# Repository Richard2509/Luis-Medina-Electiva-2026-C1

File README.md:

# Luis-Medina-Electiva-2026-C1
##  Tarea – Resumen de MBSE

En este repositorio se encuentra el resumen correspondiente a la asignatura **Electiva 2026 C1**, sobre el tema **Model-Based Systems Engineering (MBSE)** y tambien se encuentra el link de un video que tambien forma parte de la tarea.

 **Archivo adjunto:**
[Resumen de MBSE.zip](https://github.com/user-attachments/files/24985662/Resumen.de.MBSE.zip)

**Link del Video**
https://youtu.be/C6BTCFWo2lI?si=XBMWATvWH2EMt3oG

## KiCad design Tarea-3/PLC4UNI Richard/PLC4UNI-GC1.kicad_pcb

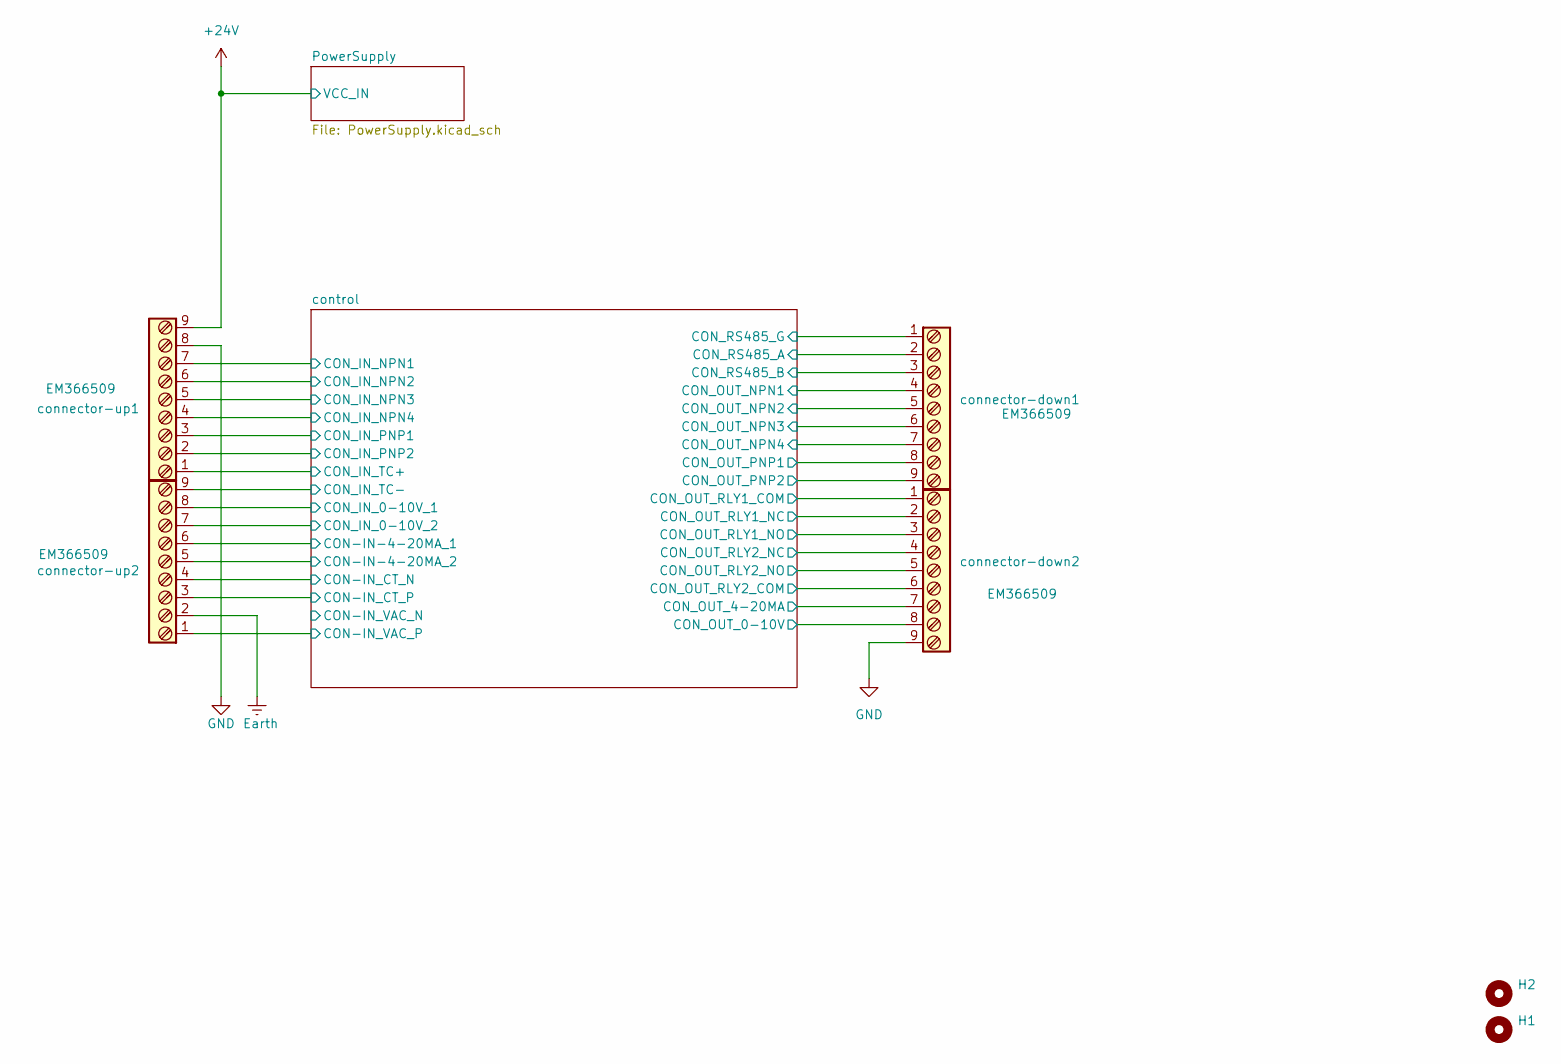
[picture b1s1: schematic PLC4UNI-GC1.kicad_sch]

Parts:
H1, H2: MountingHole; MountingHole_3.2mm_M3
connector-down1, connector-down2: Screw_Terminal_9_P5.00mm; TerminalBlock_Phoenix_PT-1,5-9-5.0-H_1x09_P5.00mm_Horizontal; Part number EM366509
connector-up1, connector-up2: Screw_Terminal_9_P5.00mm; TerminalBlock_Phoenix_PT-1,5-9-5.0-H_1x09_P5.00mm_Horizontal; Part number EM366509

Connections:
+24V: connector-up1.9; also elsewhere on the board
/control/CON-IN-4-20MA_1: connector-up2.6; also elsewhere on the board
/control/CON-IN-4-20MA_2: connector-up2.5; also elsewhere on the board
/control/CON-IN_CT_N: connector-up2.4; also elsewhere on the board
/control/CON-IN_CT_P: connector-up2.3; also elsewhere on the board
/control/CON-IN_VAC_P: connector-up2.1; also elsewhere on the board
/control/CON_IN_0-10V_1: connector-up2.8; also elsewhere on the board
/control/CON_IN_0-10V_2: connector-up2.7; also elsewhere on the board
/control/CON_IN_NPN1: connector-up1.7; also elsewhere on the board
/control/CON_IN_NPN2: connector-up1.6; also elsewhere on the board
/control/CON_IN_NPN3: connector-up1.5; also elsewhere on the board
/control/CON_IN_NPN4: connector-up1.4; also elsewhere on the board
/control/CON_IN_PNP1: connector-up1.3; also elsewhere on the board
/control/CON_IN_PNP2: connector-up1.2; also elsewhere on the board
/control/CON_IN_TC+: connector-up1.1; also elsewhere on the board
/control/CON_IN_TC-: connector-up2.9; also elsewhere on the board
/control/CON_OUT_0-10V: connector-down2.8; also elsewhere on the board
/control/CON_OUT_4-20MA: connector-down2.7; also elsewhere on the board
/control/CON_OUT_NPN1: connector-down1.4; also elsewhere on the board
/control/CON_OUT_NPN2: connector-down1.5; also elsewhere on the board
/control/CON_OUT_NPN3: connector-down1.6; also elsewhere on the board
/control/CON_OUT_NPN4: connector-down1.7; also elsewhere on the board
/control/CON_OUT_PNP1: connector-down1.8; also elsewhere on the board
/control/CON_OUT_PNP2: connector-down1.9; also elsewhere on the board
/control/CON_OUT_RLY1_COM: connector-down2.1; also elsewhere on the board
/control/CON_OUT_RLY1_NC: connector-down2.2; also elsewhere on the board
/control/CON_OUT_RLY1_NO: connector-down2.3; also elsewhere on the board
/control/CON_OUT_RLY2_COM: connector-down2.6; also elsewhere on the board
/control/CON_OUT_RLY2_NC: connector-down2.4; also elsewhere on the board
/control/CON_OUT_RLY2_NO: connector-down2.5; also elsewhere on the board
/control/CON_RS485_A: connector-down1.2; also elsewhere on the board
/control/CON_RS485_B: connector-down1.3; also elsewhere on the board
/control/CON_RS485_G: connector-down1.1; also elsewhere on the board
Earth: connector-up2.2; also elsewhere on the board
GND: connector-down2.9, connector-up1.8; also elsewhere on the board

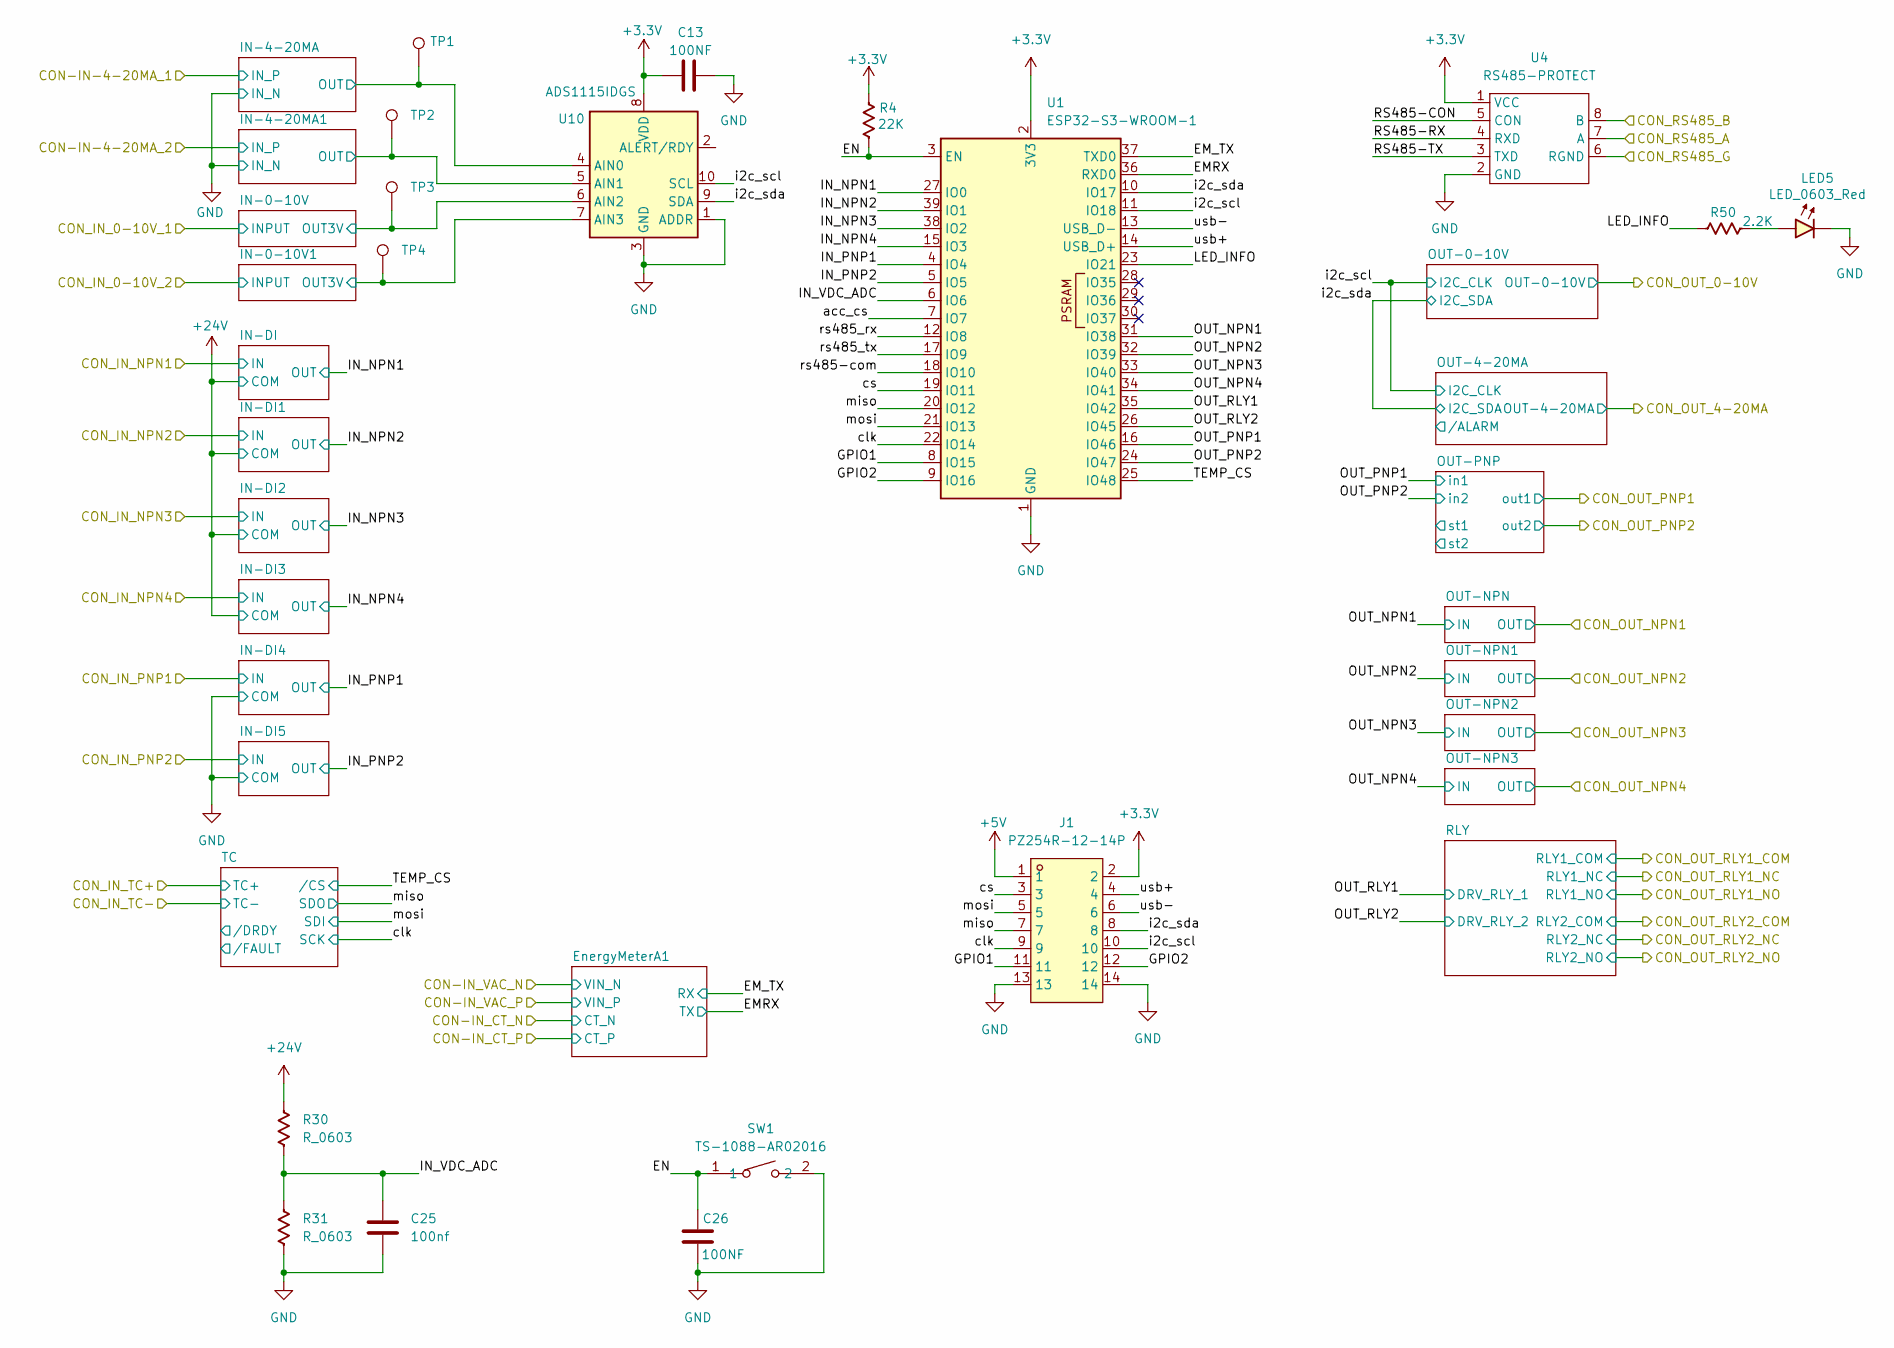
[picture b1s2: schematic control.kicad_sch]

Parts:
C13, C26: 100NF; C_0603_1608Metric
C25: 100nf; C_0603_1608Metric
J1: PZ254R-12-14P; HDR-TH_14P-P2.54-H-M-R2-C7-S2.54; LCSC Part C492435
LED5: LED_0603_Red; LED_0603_1608Metric
R4: 22K; R_0603_1608Metric
R30, R31: R_0603; R_0603_1608Metric
R50: 2.2K; R_0603_1608Metric
SW1: TS-1088-AR02016; SW-SMD_L3.9-W3.0-P4.45; LCSC Part C720477
TP1, TP2, TP3, TP4: TestPoint_Hole1; TestPoint_WireHole
U1: ESP32-S3-WROOM-1; ESP32-S3-WROOM-1U
U4: RS485-PROTECT; RS-485-PROTECT; Part Number RS-485-PROTECT
U10: ADS1115IDGS; TSSOP-10_3x3mm_P0.5mm

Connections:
+3.3V: C13.1, J1.2, R4.2, U1.2 (3V3), U4.1 (VCC), U10.8 (VDD); also elsewhere on the board
+5V: J1.1; also elsewhere on the board
+24V: R30.1; also elsewhere on the board
/control/CON_RS485_A: U4.7 (A); also elsewhere on the board
/control/CON_RS485_B: U4.8 (B); also elsewhere on the board
/control/CON_RS485_G: U4.6 (RGND); also elsewhere on the board
/control/EMRX: U1.36 (RXD0); also elsewhere on the board
/control/EM_TX: U1.37 (TXD0); also elsewhere on the board
/control/EN: C26.2, R4.1, SW1.1, U1.3 (EN)
/control/GPIO1: J1.11, U1.8 (IO15)
/control/GPIO2: J1.12, U1.9 (IO16)
/control/IN-0-10V1/OUT3V: TP4.1, U10.7 (AIN3); also elsewhere on the board
/control/IN-0-10V/OUT3V: TP3.1, U10.6 (AIN2); also elsewhere on the board
/control/IN-4-20MA1/OUT: TP2.1, U10.5 (AIN1); also elsewhere on the board
/control/IN-4-20MA/OUT: TP1.1, U10.4 (AIN0); also elsewhere on the board
/control/IN_NPN1: U1.27 (IO0); also elsewhere on the board
/control/IN_NPN2: U1.39 (IO1); also elsewhere on the board
/control/IN_NPN3: U1.38 (IO2); also elsewhere on the board
/control/IN_NPN4: U1.15 (IO3); also elsewhere on the board
/control/IN_PNP1: U1.4 (IO4); also elsewhere on the board
/control/IN_PNP2: U1.5 (IO5); also elsewhere on the board
/control/IN_VDC_ADC: C25.1, R30.2, R31.1, U1.6 (IO6)
/control/LED_INFO: R50.2, U1.23 (IO21)
/control/OUT_NPN1: U1.31 (IO38); also elsewhere on the board
/control/OUT_NPN2: U1.32 (IO39); also elsewhere on the board
/control/OUT_NPN3: U1.33 (IO40); also elsewhere on the board
/control/OUT_NPN4: U1.34 (IO41); also elsewhere on the board
/control/OUT_PNP1: U1.16 (IO46); also elsewhere on the board
/control/OUT_PNP2: U1.24 (IO47); also elsewhere on the board
/control/OUT_RLY1: U1.35 (IO42); also elsewhere on the board
/control/OUT_RLY2: U1.26 (IO45); also elsewhere on the board
/control/RS485-CON: U4.5 (CON)
/control/RS485-RX: U4.4 (RXD)
/control/RS485-TX: U4.3 (TXD)
/control/TEMP_CS: U1.25 (IO48); also elsewhere on the board
/control/acc_cs: U1.7 (IO7)
/control/clk: J1.9, U1.22 (IO14); also elsewhere on the board
/control/cs: J1.3, U1.19 (IO11)
/control/i2c_scl: J1.10, U1.11 (IO18), U10.10 (SCL); also elsewhere on the board
/control/i2c_sda: J1.8, U1.10 (IO17), U10.9 (SDA); also elsewhere on the board
/control/miso: J1.7, U1.20 (IO12); also elsewhere on the board
/control/mosi: J1.5, U1.21 (IO13); also elsewhere on the board
/control/rs485-com: U1.18 (IO10)
/control/rs485_rx: U1.12 (IO8)
/control/rs485_tx: U1.17 (IO9)
/control/usb+: J1.4, U1.14 (USB_D+)
/control/usb-: J1.6, U1.13 (USB_D-)
GND: C13.2, C25.2, C26.1, J1.13, J1.14, LED5.1 (K), R31.2, SW1.2, U1.1 (GND), U1.40 (GND), U1.41 (GND), U4.2 (GND), U10.1 (ADDR), U10.3 (GND); also elsewhere on the board
unnamed: LED5.2 (A), R50.1

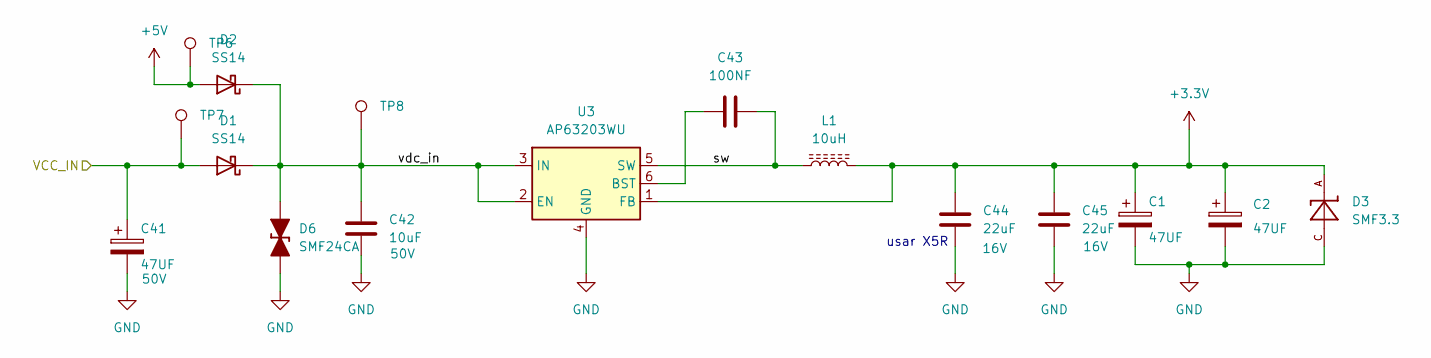
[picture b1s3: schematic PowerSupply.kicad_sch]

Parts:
C1, C2: 47UF; CP_Elec_6.3x7.7; Part Number UUD1C470MCL1GS
C41: 47UF; CP_Elec_6.3x7.7; Part Number C2887275; LCSC Part C2887275
C42: 10uF; C_0805_2012Metric; Part Number GRM21BR61H106KE43L; LCSC Part C440198
C43: 100NF; C_0805_2012Metric; Part Number CC0805KRX7R9BB104; LCSC Part C49678
C44, C45: 22uF; C_0805_2012Metric; Part Number CL21A226MOQNNNE; LCSC Part C98190
D1, D2: SS14; D_SMA
D3: SMF3.3; SMF3.3_SODFL3718X108N
D6: SMF24CA; D_SOD-123F
L1: 10uH; L_APV_APH0630; Part Number SL0630-100M; LCSC Part C22463823
TP6, TP7, TP8: TestPoint_Hole1; TestPoint_WireHole
U3: AP63203WU; TSOT-23-6

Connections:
+3.3V: C1.1, C2.1, C44.1, C45.1, D3.A, L1.2, U3.1 (FB); also elsewhere on the board
+5V: D2.2 (A), TP6.1; also elsewhere on the board
+24V: C41.1, D1.2 (A), TP7.1; also elsewhere on the board
/PowerSupply/sw: C43.2, L1.1, U3.5 (SW)
/PowerSupply/vdc_in: C42.1, D1.1 (K), D2.1 (K), D6.2 (A), TP8.1, U3.2 (EN), U3.3 (IN)
GND: C1.2, C2.2, C41.2, C42.2, C44.2, C45.2, D3.C, D6.1 (K), U3.4 (GND); also elsewhere on the board
unnamed: C43.1, U3.6 (BST)

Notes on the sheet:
usar X5R

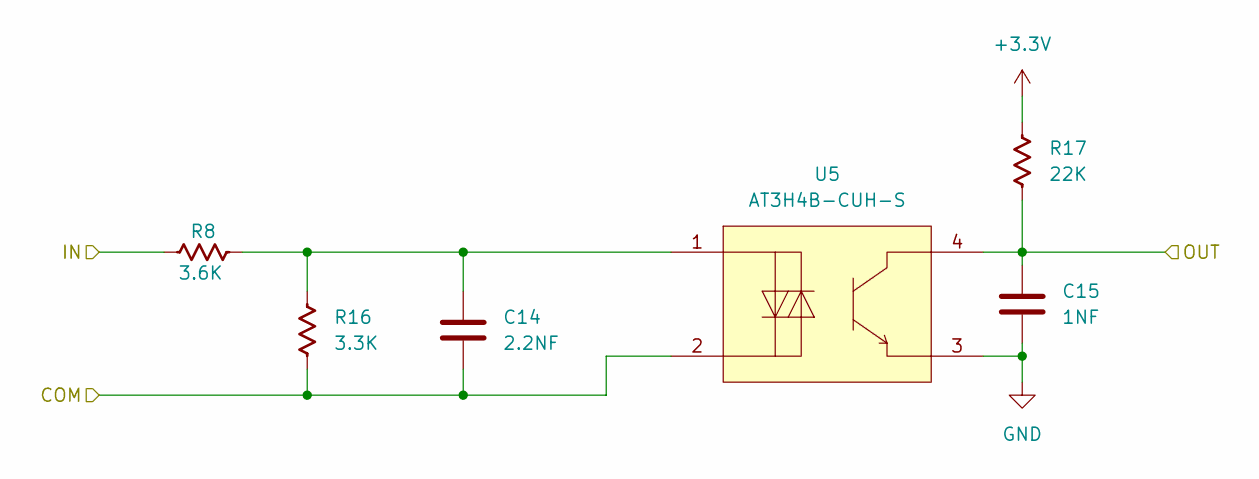
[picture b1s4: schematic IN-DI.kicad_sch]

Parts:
C14: 2.2NF; C_0603_1608Metric
C15: 1NF; C_0603_1608Metric
R8: 3.6K; R_0603_1608Metric
R16: 3.3K; R_0603_1608Metric
R17: 22K; R_0603_1608Metric
U5: AT3H4B-CUH-S; SSOP-4_L2.7-W4.6-P1.27-LS7.0-TL; LCSC Part C20612635

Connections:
+3.3V: R17.2; also elsewhere on the board
+24V: C14.2, R16.1, U5.2; also elsewhere on the board
/control/CON_IN_NPN2: R8.1; also elsewhere on the board
/control/IN_NPN2: C15.1, R17.1, U5.4; also elsewhere on the board
GND: C15.2, U5.3; also elsewhere on the board
unnamed: C14.1, R8.2, R16.2, U5.1

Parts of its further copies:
C3, C4, C16, C18, C21: 2.2NF; C_0603_1608Metric
C9, C17, C19, C20, C22: 1NF; C_0603_1608Metric
R1, R5, R18, R21, R24: 3.6K; R_0603_1608Metric
R2, R6, R19, R22, R25: 3.3K; R_0603_1608Metric
R3, R7, R20, R23, R26: 22K; R_0603_1608Metric
U2, U6, U11, U12, U14: AT3H4B-CUH-S; SSOP-4_L2.7-W4.6-P1.27-LS7.0-TL; LCSC Part C20612635

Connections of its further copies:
+3.3V: R3.2, R7.2, R20.2, R23.2, R26.2; also elsewhere on the board
+24V: C4.2, C16.2, C18.2, R6.1, R19.1, R22.1, U2.2, U11.2, U12.2; also elsewhere on the board
/control/CON_IN_NPN1: R5.1; also elsewhere on the board
/control/CON_IN_NPN3: R18.1; also elsewhere on the board
/control/CON_IN_NPN4: R21.1; also elsewhere on the board
/control/CON_IN_PNP1: R1.1; also elsewhere on the board
/control/CON_IN_PNP2: R24.1; also elsewhere on the board
/control/IN_NPN1: C9.1, R7.1, U2.4; also elsewhere on the board
/control/IN_NPN3: C17.1, R20.1, U11.4; also elsewhere on the board
/control/IN_NPN4: C19.1, R23.1, U12.4; also elsewhere on the board
/control/IN_PNP1: C20.1, R3.1, U6.4; also elsewhere on the board
/control/IN_PNP2: C22.1, R26.1, U14.4; also elsewhere on the board
GND: C3.2, C9.2, C17.2, C19.2, C20.2, C21.2, C22.2, R2.1, R25.1, U2.3, U6.2, U6.3, U11.3, U12.3, U14.2, U14.3; also elsewhere on the board
unnamed: C3.1, R1.2, R2.2, U6.1
unnamed: C4.1, R5.2, R6.2, U2.1
unnamed: C16.1, R18.2, R19.2, U11.1
unnamed: C18.1, R21.2, R22.2, U12.1
unnamed: C21.1, R24.2, R25.2, U14.1

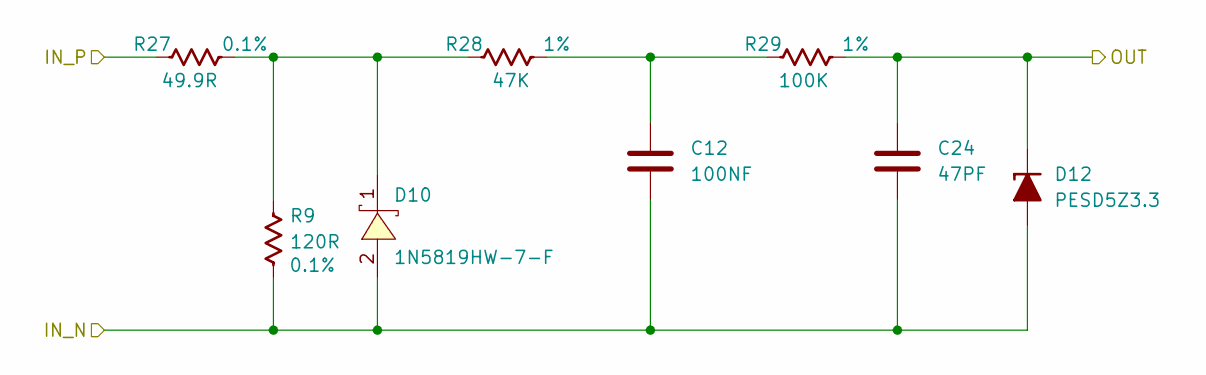
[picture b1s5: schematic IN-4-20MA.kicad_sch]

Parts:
C12: 100NF; C_0603_1608Metric
C24: 47PF; C_0603_1608Metric
D10: 1N5819HW-7-F; SOD-123_L2.7-W1.6-LS3.7-RD; LCSC Part C82544
D12: PESD5Z3.3; D_SOD-523
R9: 120R; R_0805_2012Metric
R27: 49.9R; R_0805_2012Metric
R28: 47K; R_0805_2012Metric
R29: 100K; R_0805_2012Metric

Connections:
/control/CON-IN-4-20MA_1: R27.2; also elsewhere on the board
/control/IN-4-20MA/OUT: C24.1, D12.1 (K), R29.1; also elsewhere on the board
GND: C12.2, C24.2, D10.2 (A), D12.2 (A), R9.1; also elsewhere on the board
unnamed: C12.1, R28.1, R29.2
unnamed: D10.1 (K), R9.2, R27.1, R28.2

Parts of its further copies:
C33: 100NF; C_0603_1608Metric
C34: 47PF; C_0603_1608Metric
D15: 1N5819HW-7-F; SOD-123_L2.7-W1.6-LS3.7-RD; LCSC Part C82544
D16: PESD5Z3.3; D_SOD-523
R46: 49.9R; R_0805_2012Metric
R47: 120R; R_0805_2012Metric
R48: 47K; R_0805_2012Metric
R49: 100K; R_0805_2012Metric

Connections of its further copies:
/control/CON-IN-4-20MA_2: R46.2; also elsewhere on the board
/control/IN-4-20MA1/OUT: C34.1, D16.1 (K), R49.1; also elsewhere on the board
GND: C33.2, C34.2, D15.2 (A), D16.2 (A), R47.1; also elsewhere on the board
unnamed: C33.1, R48.1, R49.2
unnamed: D15.1 (K), R46.1, R47.2, R48.2

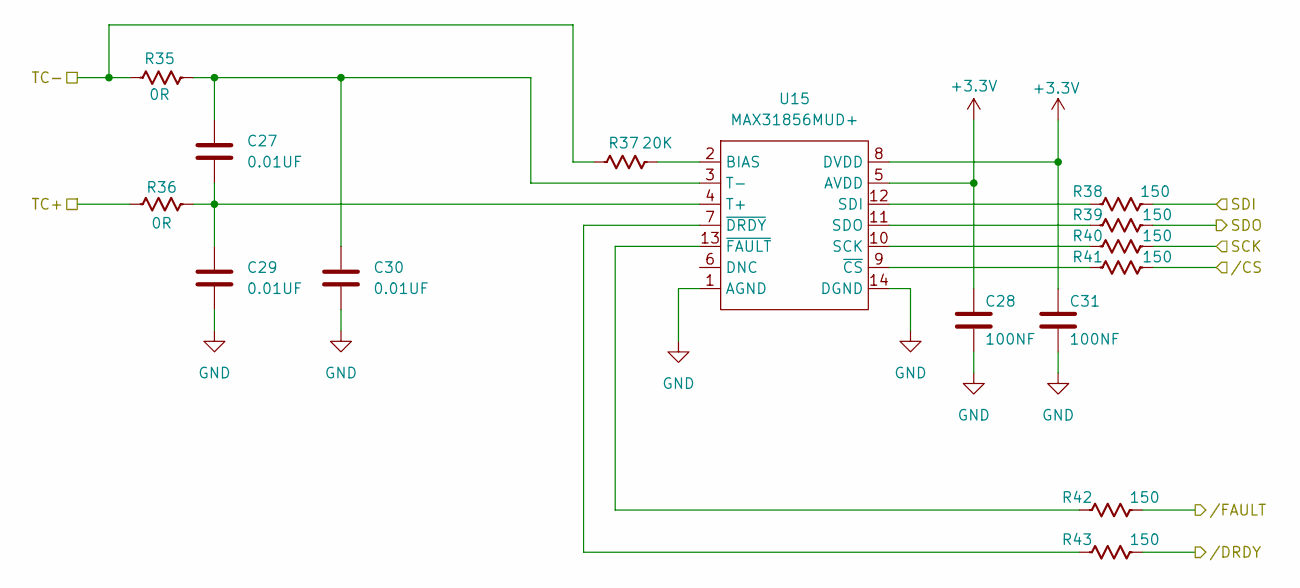
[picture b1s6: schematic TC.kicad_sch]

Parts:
C27, C29, C30: 0.01UF; C_0603_1608Metric
C28, C31: 100NF; C_0603_1608Metric
R35, R36: 0R; R_0603_1608Metric
R37: 20K; R_0603_1608Metric
R38, R39, R40, R41, R42, R43: 150; R_0603_1608Metric
U15: MAX31856MUD+; TSSOP-14_L5.0-W4.4-P0.65-LS6.4-BL; LCSC Part C116632

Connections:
+3.3V: C28.1, C31.1, U15.5 (AVDD), U15.8 (DVDD); also elsewhere on the board
/control/CON_IN_TC+: R36.1; also elsewhere on the board
/control/CON_IN_TC-: R35.1, R37.1; also elsewhere on the board
/control/TC//DRDY: R43.2
/control/TC//FAULT: R42.2
/control/TEMP_CS: R41.2; also elsewhere on the board
/control/clk: R40.2; also elsewhere on the board
/control/miso: R39.2; also elsewhere on the board
/control/mosi: R38.2; also elsewhere on the board
GND: C28.2, C29.2, C30.2, C31.2, U15.1 (AGND), U15.14 (DGND); also elsewhere on the board
unnamed: R37.2, U15.2 (BIAS)
unnamed: R40.1, U15.10 (SCK)
unnamed: R38.1, U15.12 (SDI)
unnamed: R39.1, U15.11 (SDO)
unnamed: C27.2, C29.1, R36.2, U15.4 (T+)
unnamed: C27.1, C30.1, R35.2, U15.3 (T-)
unnamed: R41.1, U15.9 (~CS)
unnamed: R43.1, U15.7 (~DRDY)
unnamed: R42.1, U15.13 (~FAULT)

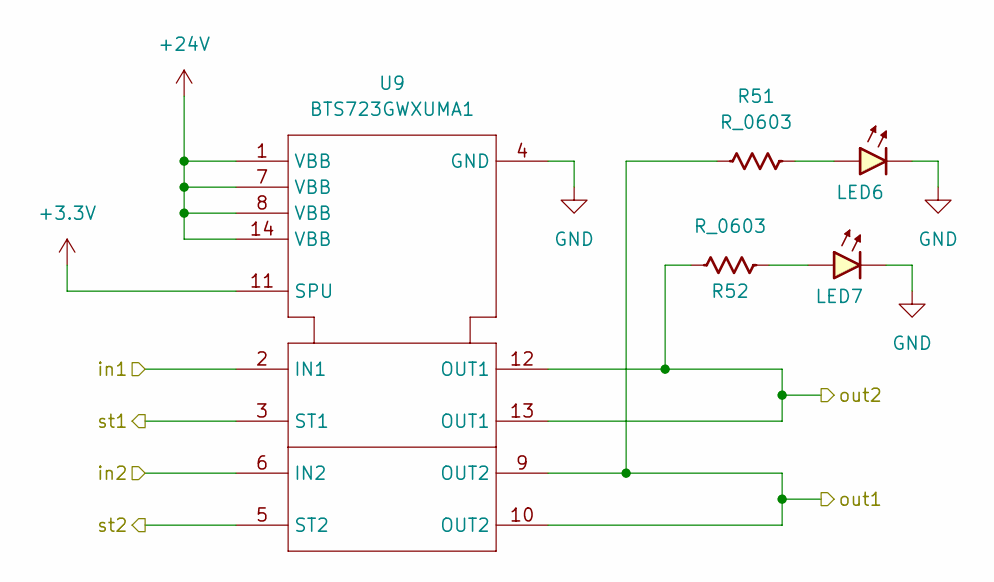
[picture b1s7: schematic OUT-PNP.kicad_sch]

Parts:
LED6, LED7: LED_0603_Red; LED_0603_1608Metric
R51, R52: R_0603; R_0603_1608Metric
U9: BTS723GWXUMA1; SOIC-14_L8.7-W3.9-P1.27-LS6.0-BL; LCSC Part C67625

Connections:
+3.3V: U9.11 (SPU); also elsewhere on the board
+24V: U9.1 (VBB), U9.7 (VBB), U9.8 (VBB), U9.14 (VBB); also elsewhere on the board
/control/CON_OUT_PNP1: R51.1, U9.9 (OUT2), U9.10 (OUT2); also elsewhere on the board
/control/CON_OUT_PNP2: R52.1, U9.12 (OUT1), U9.13 (OUT1); also elsewhere on the board
/control/OUT-PNP/st1: U9.3 (ST1)
/control/OUT-PNP/st2: U9.5 (ST2)
/control/OUT_PNP1: U9.2 (IN1); also elsewhere on the board
/control/OUT_PNP2: U9.6 (IN2); also elsewhere on the board
GND: LED6.1 (K), LED7.1 (K), U9.4 (GND); also elsewhere on the board
unnamed: LED6.2 (A), R51.2
unnamed: LED7.2 (A), R52.2

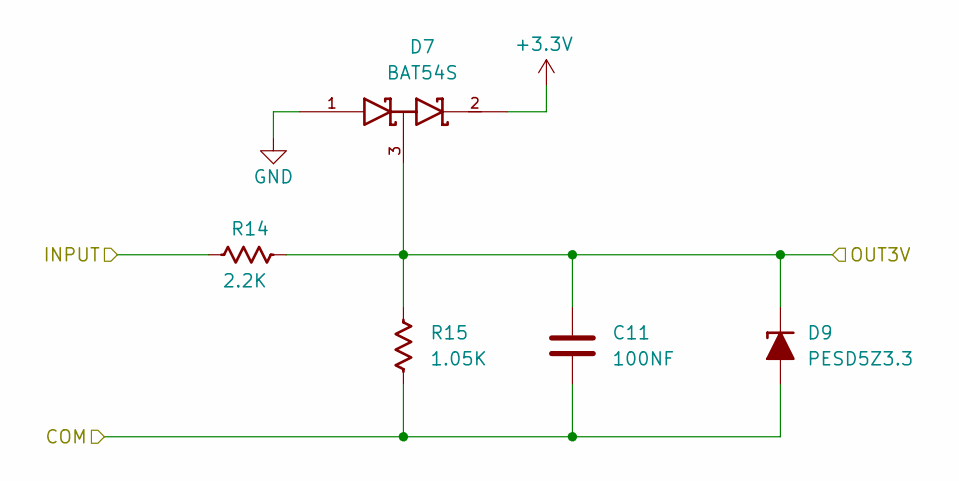
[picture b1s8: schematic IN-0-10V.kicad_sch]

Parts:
C11: 100NF; C_0603_1608Metric
D7: BAT54S; SOT23-3_PO132; Part Number BAT54S-7-F; JLCPCB ID C83574
D9: PESD5Z3.3; D_SOD-523
R14: 2.2K; R_0603_1608Metric
R15: 1.05K; R_0603_1608Metric

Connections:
+3.3V: D7.2 (cathode); also elsewhere on the board
/control/CON_IN_0-10V_1: R14.1; also elsewhere on the board
/control/IN-0-10V/COM: C11.2, D9.2 (A), R15.2
/control/IN-0-10V/OUT3V: C11.1, D7.3 (AK), D9.1 (K), R14.2, R15.1; also elsewhere on the board
GND: D7.1 (Anode); also elsewhere on the board

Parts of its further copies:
C32: 100NF; C_0603_1608Metric
D13: BAT54S; SOT23-3_PO132; Part Number BAT54S-7-F; JLCPCB ID C83574
D14: PESD5Z3.3; D_SOD-523
R44: 2.2K; R_0603_1608Metric
R45: 1.05K; R_0603_1608Metric

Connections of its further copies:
+3.3V: D13.2 (cathode); also elsewhere on the board
/control/CON_IN_0-10V_2: R44.1; also elsewhere on the board
/control/IN-0-10V1/COM: C32.2, D14.2 (A), R45.2
/control/IN-0-10V1/OUT3V: C32.1, D13.3 (AK), D14.1 (K), R44.2, R45.1; also elsewhere on the board
GND: D13.1 (Anode); also elsewhere on the board

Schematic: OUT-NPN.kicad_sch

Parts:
LED3: LED_0603_Red; LED_0603_1608Metric
Q5: ZXMS6004FFQTA; SOT-23-3; Part Number ZXMS6004FFQTA
R13: R_0603; R_0603_1608Metric

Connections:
+24V: R13.1; also elsewhere on the board
/control/CON_OUT_NPN1: LED3.1 (K), Q5.3 (D); also elsewhere on the board
/control/OUT_NPN1: Q5.1 (IN); also elsewhere on the board
GND: Q5.2 (OUT); also elsewhere on the board
unnamed: LED3.2 (A), R13.2

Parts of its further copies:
LED1, LED2, LED4: LED_0603_Red; LED_0603_1608Metric
Q2, Q3, Q4: ZXMS6004FFQTA; SOT-23-3; Part Number ZXMS6004FFQTA
R32, R33, R34: R_0603; R_0603_1608Metric

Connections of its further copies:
+24V: R32.1, R33.1, R34.1; also elsewhere on the board
/control/CON_OUT_NPN2: LED1.1 (K), Q2.3 (D); also elsewhere on the board
/control/CON_OUT_NPN3: LED2.1 (K), Q3.3 (D); also elsewhere on the board
/control/CON_OUT_NPN4: LED4.1 (K), Q4.3 (D); also elsewhere on the board
/control/OUT_NPN2: Q2.1 (IN); also elsewhere on the board
/control/OUT_NPN3: Q3.1 (IN); also elsewhere on the board
/control/OUT_NPN4: Q4.1 (IN); also elsewhere on the board
GND: Q2.2 (OUT), Q3.2 (OUT), Q4.2 (OUT); also elsewhere on the board
unnamed: LED1.2 (A), R32.2
unnamed: LED2.2 (A), R33.2
unnamed: LED4.2 (A), R34.2

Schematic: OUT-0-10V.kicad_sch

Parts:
C5, C6: C_0603; C_0603_1608Metric
C10: 100nF; C_0603_1608Metric
D8: SD12_SOD323; D_SOD-323
U7: GP8211S-TC50-EW; ESOP-8_L4.9-W3.9-P1.27-LS6.0-BL-EP; LCSC Part C3152008

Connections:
+24V: C5.1, U7.4 (VCC); also elsewhere on the board
/control/CON_OUT_0-10V: C10.1, D8.2 (A2), U7.6 (VOUT); also elsewhere on the board
/control/i2c_scl: U7.1 (SCLK); also elsewhere on the board
/control/i2c_sda: U7.2 (SDA); also elsewhere on the board
GND: C5.2, C6.2, C10.2, D8.1 (A1), U7.5 (GND), U7.9 (EP); also elsewhere on the board
unnamed: C6.1, U7.8 (V5V)

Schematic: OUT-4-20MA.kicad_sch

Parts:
C7, C23: C_0603; C_0603_1608Metric
C8: 1uF; C_0603_1608Metric
D4: DSK120_C22466355; SOD-123FL_L2.7-W1.8-LS3.8-RD; LCSC Part C22466355
D5: SMBJ28A; D_SMB
D11: SMAJ12A; D_SMA
Q1: NCE60P04R; SOT-223-3_L6.5-W3.4-P2.30-LS7.0-BR; LCSC Part C502855
R10: R_0603; R_0603_1608Metric
R11: 15R; R_0805_2012Metric
R12: 470K; R_0603_1608Metric
U8: GP8302-TC50-EW; ESOP-8_L4.9-W3.9-P1.27-LS6.0-BL-EP; LCSC Part C2856295

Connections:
+24V: C23.1, D11.1 (A1), U8.4 (VCC); also elsewhere on the board
/control/CON_OUT_4-20MA: D4.1 (C); also elsewhere on the board
/control/OUT-4-20MA//ALARM: U8.3 (~ALARM)
/control/i2c_scl: U8.1 (SLCK); also elsewhere on the board
/control/i2c_sda: U8.2 (SDA); also elsewhere on the board
GND: C7.2, C8.2, C23.2, D5.2 (A), R10.2, R12.2, U8.5 (GND), U8.9 (EP); also elsewhere on the board
unnamed: D4.2 (A), R11.2
unnamed: D5.1 (K), Q1.2, Q1.4, R11.1
unnamed: C8.1, D11.2 (A2), Q1.1, R12.1
unnamed: Q1.3, U8.7 (IOUT)
unnamed: R10.1, U8.6 (SET)
unnamed: C7.1, U8.8 (V5V)

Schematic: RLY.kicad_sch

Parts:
K1, K2: G5V-1; Relay_SPDT_Omron_G5V-1
U13: LK1802; SOT-23-6_L2.9-W1.6-P0.95-LS2.8-BR; LCSC Part C2984831

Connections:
+24V: K1.2, K2.2, U13.5 (COM); also elsewhere on the board
/control/CON_OUT_RLY1_COM: K1.5, K1.6; also elsewhere on the board
/control/CON_OUT_RLY1_NC: K1.1; also elsewhere on the board
/control/CON_OUT_RLY1_NO: K1.10; also elsewhere on the board
/control/CON_OUT_RLY2_COM: K2.5, K2.6; also elsewhere on the board
/control/CON_OUT_RLY2_NC: K2.1; also elsewhere on the board
/control/CON_OUT_RLY2_NO: K2.10; also elsewhere on the board
/control/OUT_RLY1: U13.3 (1B); also elsewhere on the board
/control/OUT_RLY2: U13.4 (2B); also elsewhere on the board
GND: U13.2 (E); also elsewhere on the board
unnamed: K2.9, U13.1 (1C)
unnamed: K1.9, U13.6 (2C)

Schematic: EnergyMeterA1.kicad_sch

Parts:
C35, C36: 33NF; C_0603_1608Metric
C37: 68NF; C_0603_1608Metric
C38, C39, C40: 100NF; C_0603_1608Metric
R53, R54: 0.51; R_0805_2012Metric
R55, R56: 1K; R_0603_1608Metric
R57, R59, R60, R61, R62: 390K; R_0603_1608Metric
R58: 510; R_0603_1608Metric
R63, R64, R65, R66: 4.7K; R_0603_1608Metric
TP5, TP9, TP10, TP11: TestPoint_Hole1; TestPoint_WireHole
U16: BL0942; SSOP-10_L4.9-W3.9-P1.00-LS6.0-BL; LCSC Part C2837510
U17: B0303S-1WR3_C7465185; PWRM-TH_BXXXXS-1WR3; LCSC Part C7465185
U18: ISO7021DR; SOIC-8_L4.9-W3.9-P1.27-LS6.0-BL; LCSC Part C2867957

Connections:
+3.3V: C40.2, R65.2, R66.2, U17.2 (+Vin), U18.1 (VCC1); also elsewhere on the board
/control/CON-IN_CT_N: R54.2, R56.1; also elsewhere on the board
/control/CON-IN_CT_P: R53.1, R55.1; also elsewhere on the board
/control/CON-IN_VAC_P: R57.1; also elsewhere on the board
/control/EMRX: R66.1, U18.2 (OUTA); also elsewhere on the board
/control/EM_TX: R65.1, U18.3 (INB); also elsewhere on the board
Earth: C35.1, C36.2, C37.1, C38.1, C39.1, R53.2, R54.1, R58.1, U16.5 (GND), U16.7 (SEL), U17.3 (-Vout), U18.5 (GND2); also elsewhere on the board
GND: C40.1, U17.1 (-Vin), U18.4 (GND1); also elsewhere on the board
unnamed: R57.2, R59.1
unnamed: R59.2, R60.1
unnamed: R60.2, R61.1
unnamed: R61.2, R62.1
unnamed: C36.1, R56.2, TP11.1, U16.3 (IN)
unnamed: C35.2, R55.2, TP10.1, U16.2 (IP)
unnamed: R63.1, U16.9 (RX/SDI), U18.6 (OUTB)
unnamed: R64.1, U16.10 (TX/SDO), U18.7 (INA)
unnamed: C37.2, R58.2, R62.2, TP9.1, U16.4 (VP)
VCC: C38.2, C39.2, R63.2, R64.2, TP5.1, U16.1 (VDD), U16.8 (SCLK_BPS), U17.4 (+Vout), U18.8 (VCC2)

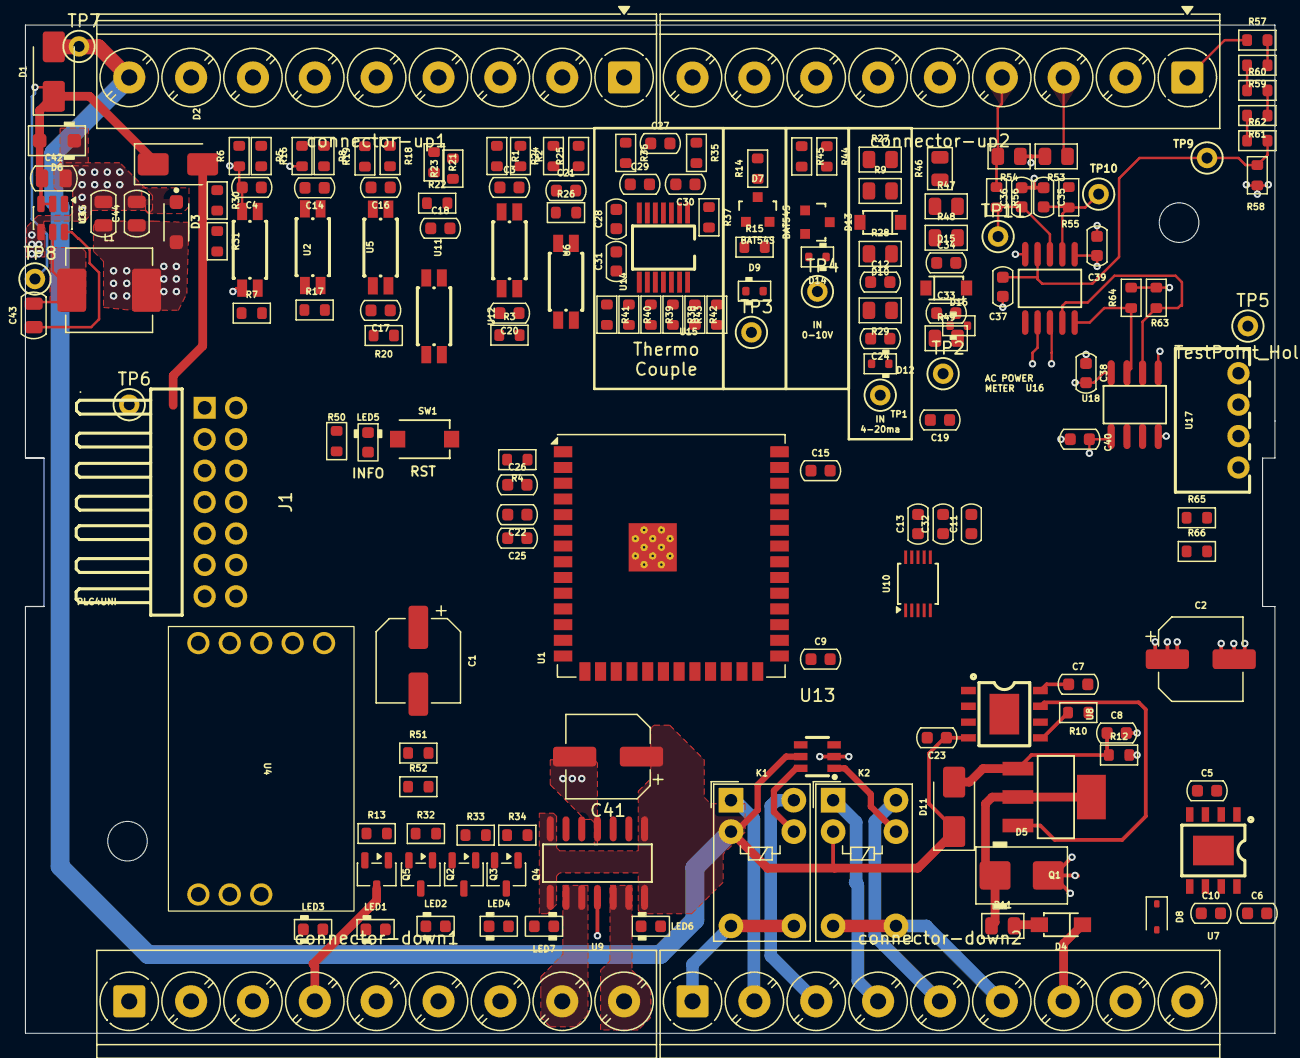
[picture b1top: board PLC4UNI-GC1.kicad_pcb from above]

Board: 4 copper layers, 101.0 x 81.5 mm, 179 parts (0 on the bottom side), 121 nets.

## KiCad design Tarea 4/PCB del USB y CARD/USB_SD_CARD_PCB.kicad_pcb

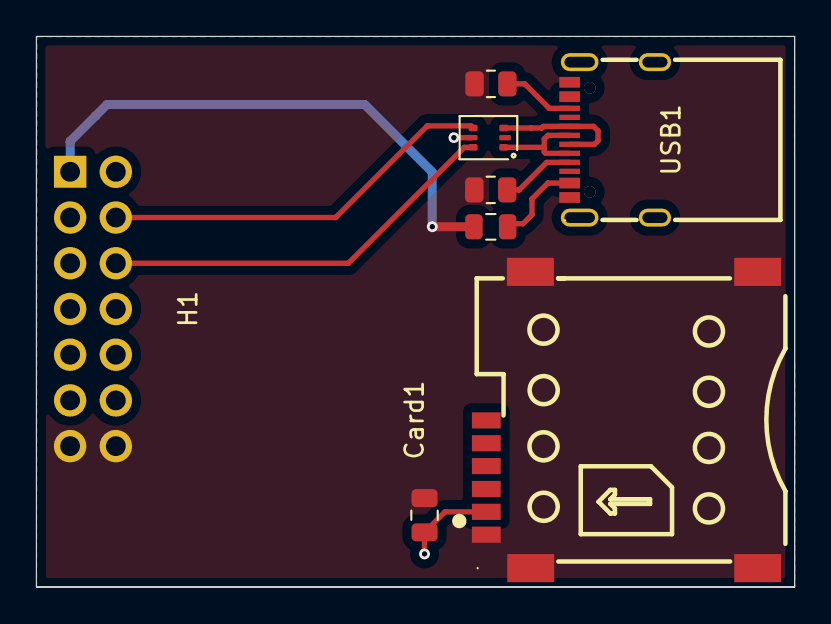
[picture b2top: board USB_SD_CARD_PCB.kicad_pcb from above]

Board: 2 copper layers, 42.1 x 30.6 mm, 8 parts (0 on the bottom side), 12 nets.

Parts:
C3: 100nf; C_0805_2012Metric
Card1: SMC-202-6; SIM-SMD_SMC-202-6
D1: USBLC6-2P6; SOT-666
F1: Polyfuse_Small; Fuse_0805_2012Metric
H1: PZ254R-12-14P; HDR-TH_14P-P2.54-H-M-R2-C7-S2.54
R1, R2: 5.1k; R_0805_2012Metric
USB1: LCK-TCF809-L117YL-G1; USB-C-SMD_LCK-TCF809-L117YL-G1

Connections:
+3.3V: C3.1, Card1.C1 (VCC), D1.5 (VP), H1.2
+5V: F1.1, H1.1
/D+: D1.3 (L2), USB1.A6 (DP1), USB1.B6 (DP2)
/D-: D1.1 (L1), USB1.A7 (DN1), USB1.B7 (DN2)
/GPIO1: Card1.C7 (I/O), H1.11
/clk: Card1.C3 (CLK), H1.9
/usb+: D1.4 (L2), H1.4
/usb-: D1.6 (L1), H1.6
GND: C3.2, Card1.7 (GND), Card1.8 (GND), Card1.9 (GND), Card1.10 (GND), Card1.C5 (GND), D1.2 (VN), H1.13, H1.14, R1.2, R2.2, USB1.A1 (GND), USB1.B1 (GND)
unnamed: F1.2, USB1.A4 (VBUS), USB1.B4 (VBUS)
unnamed: R1.1, USB1.A5 (CC1)
unnamed: R2.1, USB1.B5 (CC2)

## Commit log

2026-01-31 Create Tarea 1
2026-01-31 Tarea 1
2026-02-06 Tarea 2
    Diseños del Case del PLC4uni
2026-02-06 Tarea 2
2026-02-10 Tarea 3
